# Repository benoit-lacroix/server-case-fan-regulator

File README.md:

# Server Case Fan Regulator

Fan system for server case.

This project includes:
- Schematics and PCB design (KiCAD)
- Software (Arduino Sketch)

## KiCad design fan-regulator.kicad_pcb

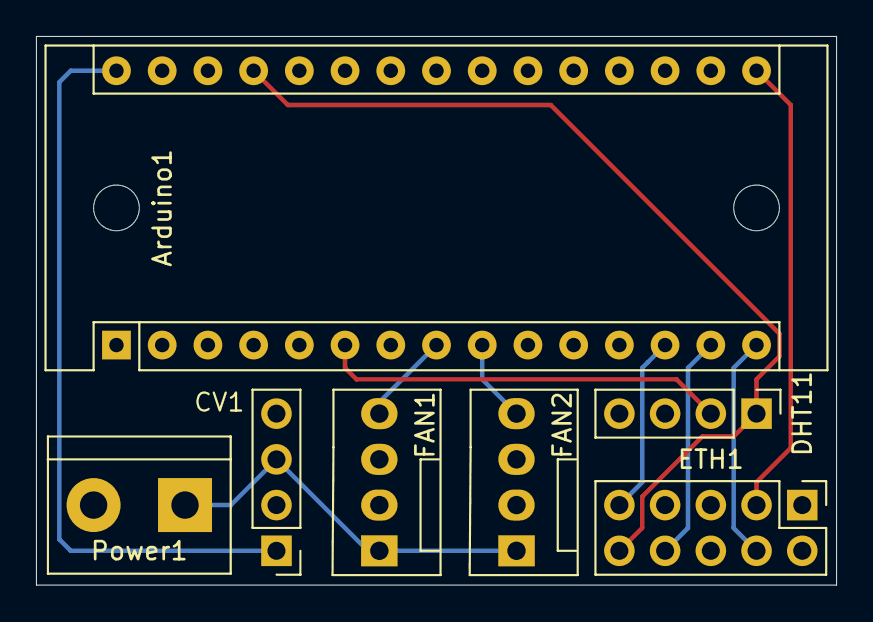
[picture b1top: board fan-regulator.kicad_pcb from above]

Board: 2 copper layers, 44.5 x 30.5 mm, 7 parts (0 on the bottom side), 11 nets.

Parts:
Arduino1: Arduino_Nano_v3.x; Arduino_Nano
CV1: Conn_01x04; Pin_Header_Straight_1x04_Pitch2.54mm
DHT11: Conn_01x04_Female; Pin_Header_Straight_1x04_Pitch2.54mm
ETH1: Conn_02x05_Counter_Clockwise; Pin_Header_Straight_2x05_Pitch2.54mm
FAN1, FAN2: Conn_01x04; Fan_Pin_Header_Straight_1x04
Power1: 12V; TerminalBlock_bornier-2_P5.08mm

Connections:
5V: Arduino1.27, DHT11.1, ETH1.10
+5V: Arduino1.30, CV1.1
+12V: CV1.3, FAN1.1, FAN2.1, Power1.1
D_DHT: Arduino1.6, DHT11.2
E_MISO: Arduino1.15, ETH1.4
E_MOSI: Arduino1.14, ETH1.8
E_NSS: Arduino1.13, ETH1.9
E_SCK: Arduino1.16, ETH1.3
FAN_PWM_1: Arduino1.8, FAN1.4
FAN_PWM_2: Arduino1.9, FAN2.4
GND: Arduino1.4, Arduino1.29, DHT11.4, ETH1.1, FAN1.2, FAN2.2, Power1.2

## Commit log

2020-12-29 Initial Commit
    Adding .gitignore, README and License
    Adding KiCAD project
2021-11-09 Cleaning and Adding Sketch
    Adding directories:
    - `ecad` for KiCAD files
    - `sketch` for Arduino sketch
